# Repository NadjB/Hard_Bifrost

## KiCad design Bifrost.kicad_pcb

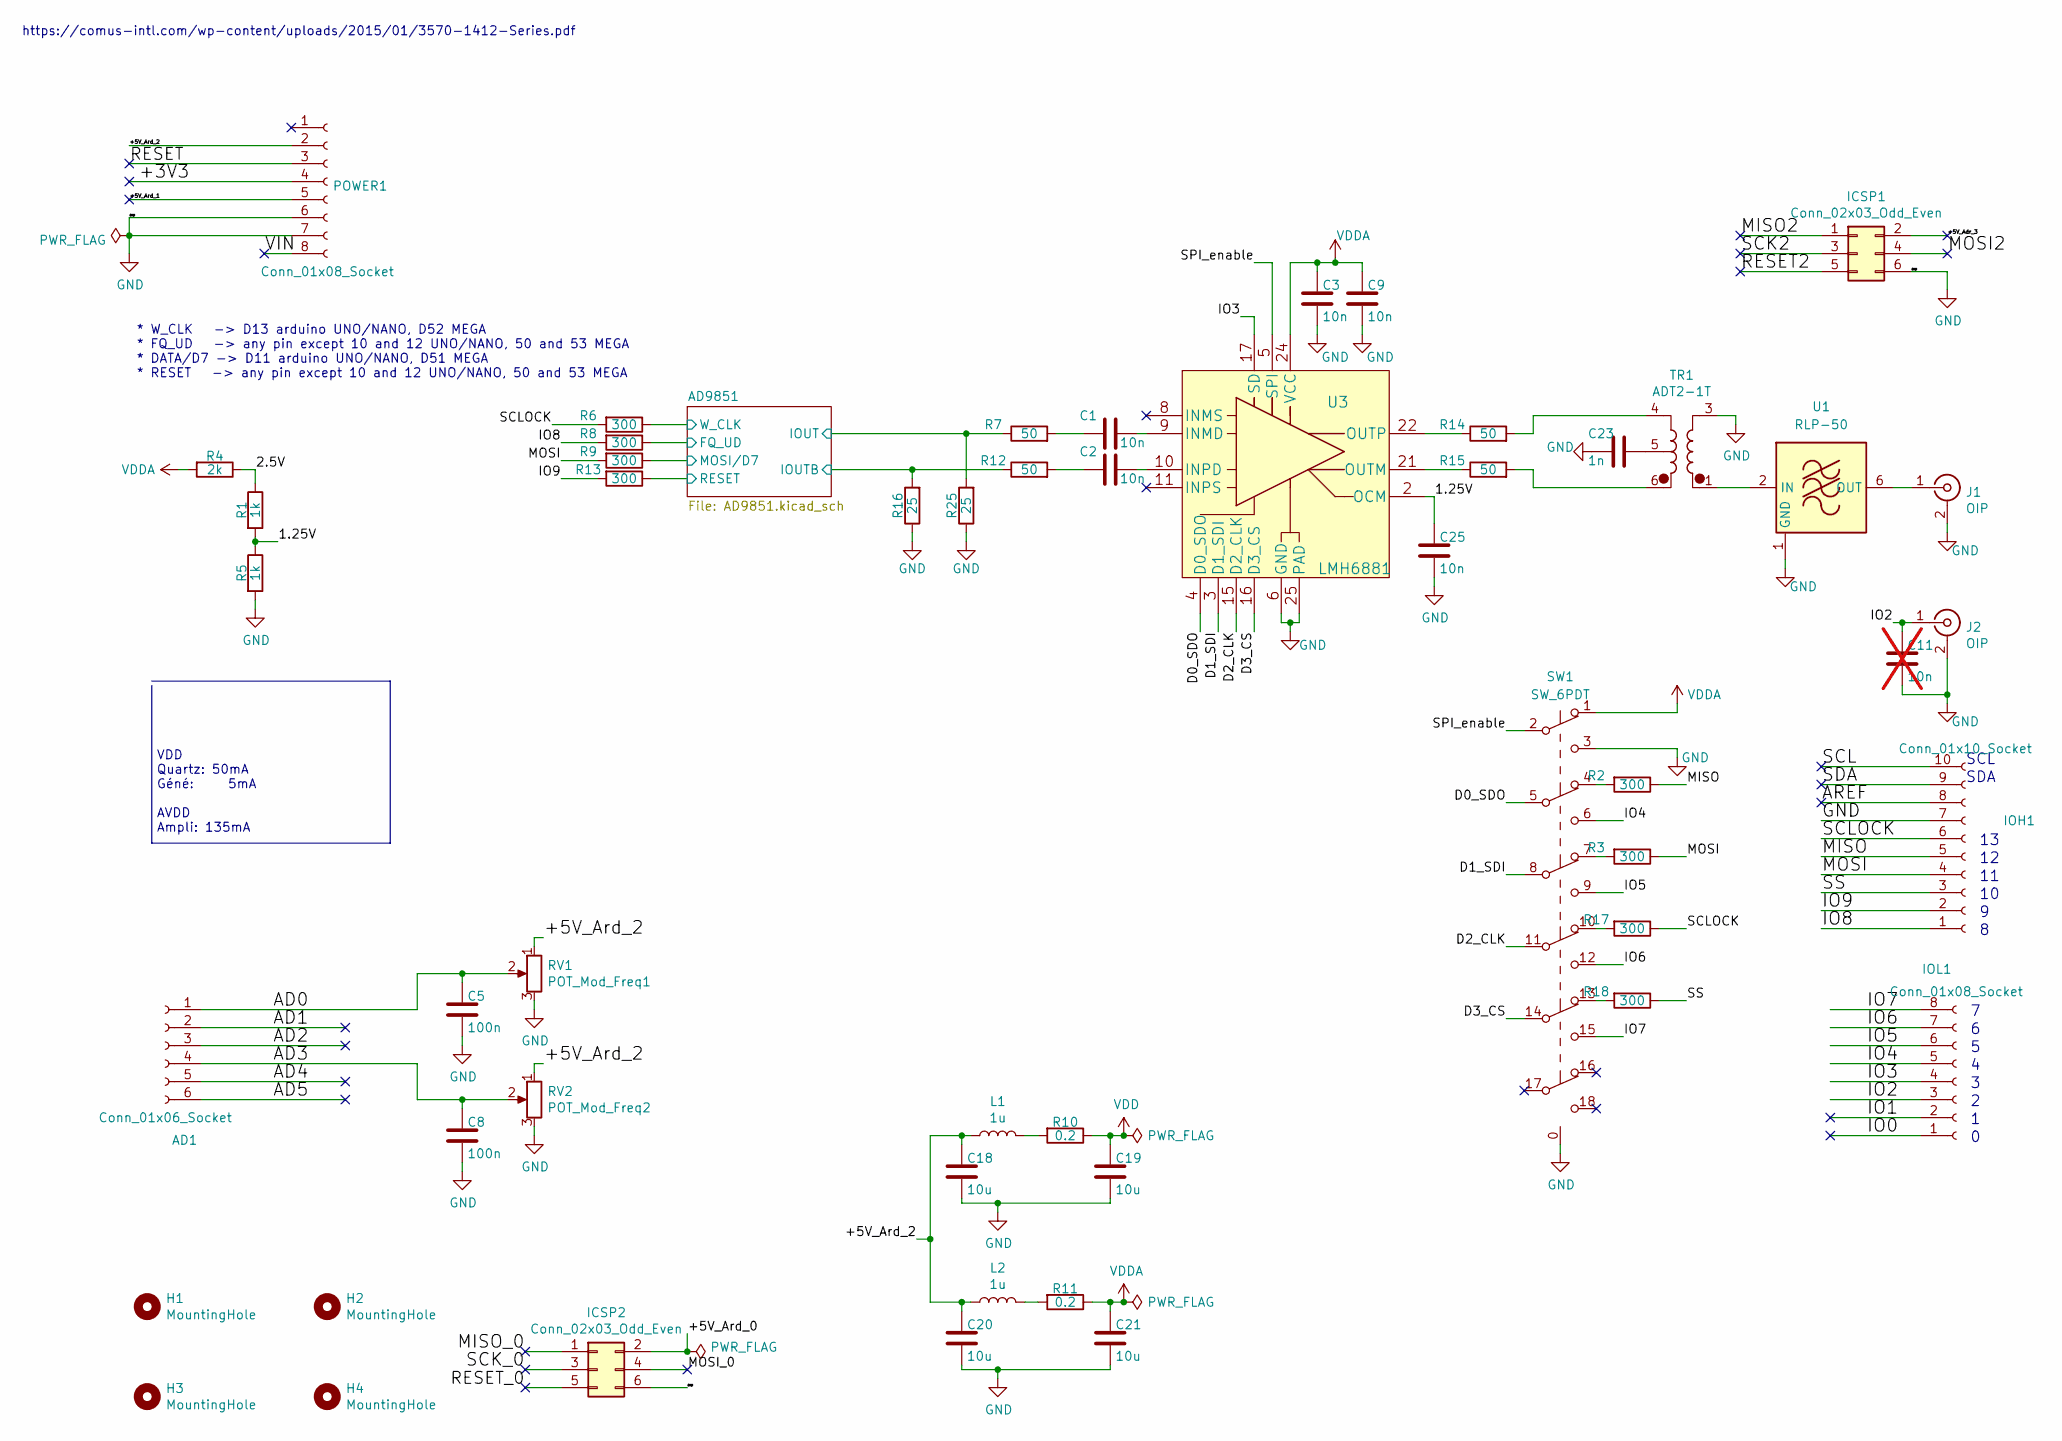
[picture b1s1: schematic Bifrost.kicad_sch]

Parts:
AD1: Conn_01x06_Socket; PinHeader_1x06_P2.54mm_Vertical
C1, C2, C3, C9, C25: 10n; C_0603_1608Metric_Pad1.08x0.95mm_HandSolder
C5, C8: 100n; C_0603_1608Metric_Pad1.08x0.95mm_HandSolder
C11: 10n; C_0603_1608Metric_Pad1.08x0.95mm_HandSolder; not fitted
C18, C19, C20, C21: 10u; C_1206_3216Metric_Pad1.33x1.80mm_HandSolder
C23: 1n; C_0603_1608Metric_Pad1.08x0.95mm_HandSolder
H1, H2, H3, H4: MountingHole; MountingHole_3mm
ICSP1, ICSP2: Conn_02x03_Odd_Even; PinSocket_2x03_P2.54mm_Vertical
IOH1: Conn_01x10_Socket; PinHeader_1x10_P2.54mm_Vertical
IOL1: Conn_01x08_Socket; PinHeader_1x08_P2.54mm_Vertical
J1, J2: OIP; SMA_Molex_73251-1153_EdgeMount_Horizontal
L1, L2: 1u; L_0603_1608Metric_Pad1.05x0.95mm_HandSolder
POWER1: Conn_01x08_Socket; PinHeader_1x08_P2.54mm_Vertical
R1, R5: 1k; R_0603_1608Metric_Pad0.98x0.95mm_HandSolder
R2, R3, R6, R8, R9, R13, R17, R18: 300; R_0603_1608Metric_Pad0.98x0.95mm_HandSolder
R4: 2k; R_0603_1608Metric_Pad0.98x0.95mm_HandSolder
R7, R12, R14, R15: 50; R_0603_1608Metric_Pad0.98x0.95mm_HandSolder
R10, R11: 0.2; R_0603_1608Metric_Pad0.98x0.95mm_HandSolder
R16, R25: 25; R_0603_1608Metric_Pad0.98x0.95mm_HandSolder
RV1: POT_Mod_Freq1; Potentiometer_Bourns_3266Y_Vertical
RV2: POT_Mod_Freq2; Potentiometer_Bourns_3266Y_Vertical
SW1: SW_6PDT; SW_EG6201
TR1: ADT2-1T; Mini-Circuits_CD542_H2.84mm
U1: RLP-50; Mini-Circuits_GP1212_LandPatternPL-176
U3: LMH6881; WQFN-24-1EP_4x4mm_P0.5mm_EP2.45x2.45mm_ThermalVias

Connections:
/1.25V: C25.2, R1.2, R5.1, U3.2 (OCM)
/2.5V: R1.1, R4.1
/+3V3: POWER1.4
/+5V_Adr_3: ICSP1.2
/+5V_Ard_0: ICSP2.2
/+5V_Ard_1: POWER1.5
/+5V_Ard_2: C18.2, C20.2, L1.1, L2.1, POWER1.2, RV1.1, RV2.1
/AD0: AD1.1, C5.2, RV1.2
/AD1: AD1.2
/AD2: AD1.3
/AD3: AD1.4, C8.2, RV2.2
/AD4: AD1.5
/AD5: AD1.6
/AD9851/FQ_UD: R8.1; also elsewhere on the board
/AD9851/IOUT: R7.1, R25.2; also elsewhere on the board
/AD9851/IOUTB: R12.1, R16.2; also elsewhere on the board
/AD9851/MOSI/D7: R9.1; also elsewhere on the board
/AD9851/RESET: R13.1; also elsewhere on the board
/AD9851/W_CLK: R6.1; also elsewhere on the board
/AREF: IOH1.8
/D0_SDO: SW1.5 (B), U3.4 (D0_SDO)
/D1_SDI: SW1.8 (B), U3.3 (D1_SDI)
/D2_CLK: SW1.11 (B), U3.15 (D2_CLK)
/D3_CS: SW1.14 (B), U3.16 (D3_CS)
/IO0: IOL1.1
/IO1: IOL1.2
/IO2: C11.2, IOL1.3, J2.1 (In)
/IO3: IOL1.4, U3.17 (SD)
/IO4: IOL1.5, SW1.6 (C)
/IO5: IOL1.6, SW1.9 (C)
/IO6: IOL1.7, SW1.12 (C)
/IO7: IOL1.8, SW1.15 (C)
/IO8: IOH1.1, R8.2
/IO9: IOH1.2, R13.2
/MISO: IOH1.5, R2.1
/MISO2: ICSP1.1
/MISO_0: ICSP2.1
/MOSI: IOH1.4, R3.1, R9.2
/MOSI2: ICSP1.4
/MOSI_0: ICSP2.4
/RESET: POWER1.3
/RESET2: ICSP1.5
/RESET_0: ICSP2.5
/SCK2: ICSP1.3
/SCK_0: ICSP2.3
/SCL: IOH1.10
/SCLOCK: IOH1.6, R6.2, R17.1
/SDA: IOH1.9
/SPI_enable: SW1.2 (B), U3.5 (SPI)
/SS: IOH1.3, R18.1
/VIN: POWER1.8
GND: C3.1, C5.1, C8.1, C9.1, C11.1, C18.1, C19.1, C20.1, C21.1, C23.1, C25.1, ICSP1.6, ICSP2.6, IOH1.7, J1.2 (Ext), J2.2 (Ext), POWER1.6, POWER1.7, R5.2, R16.1, R25.1, RV1.3, RV2.3, SW1.0, SW1.3 (C), TR1.3, U1.1 (GND), U1.3 (GND), U1.4 (GND), U1.5 (GND), U1.7 (GND), U1.8 (GND), U3.6 (GND), U3.7 (GND), U3.12 (GND), U3.13 (GND), U3.25 (PAD); also elsewhere on the board
unnamed: C1.1, R7.2
unnamed: C2.1, R12.2
unnamed: C23.2, TR1.5
unnamed: J1.1 (In), U1.6 (OUT)
unnamed: L1.2, R10.2
unnamed: L2.2, R11.2
unnamed: R2.2, SW1.4 (A)
unnamed: R3.2, SW1.7 (A)
unnamed: R14.2, TR1.4
unnamed: R15.2, TR1.6
unnamed: R17.2, SW1.10 (A)
unnamed: R18.2, SW1.13 (A)
unnamed: TR1.1, U1.2 (IN)
unnamed: C1.2, U3.9 (INMD)
unnamed: C2.2, U3.10 (INPD)
unnamed: R15.1, U3.21 (OUTM)
unnamed: R14.1, U3.22 (OUTP)
VDD: C19.2, R10.1; also elsewhere on the board
VDDA: C3.2, C9.2, C21.2, R4.2, R11.1, SW1.1 (A), U3.19 (VCC), U3.20 (VCC), U3.23 (VCC), U3.24 (VCC)

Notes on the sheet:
VDD Quartz: 50mA Géné: 5mA AVDD Ampli: 135mA
SDA
https://comus-intl.com/wp-content/uploads/2015/01/3570-1412-Series.pdf
* W_CLK -> D13 arduino UNO/NANO, D52 MEGA * FQ_UD -> any pin except 10 and 12 UNO/NANO, 50 and 53 MEGA * DATA/D7 -> D11 arduino UNO/NANO, D51 MEGA * RESET -> any pin except 10 and 12 UNO/NANO, 50 and 53 MEGA
SCL

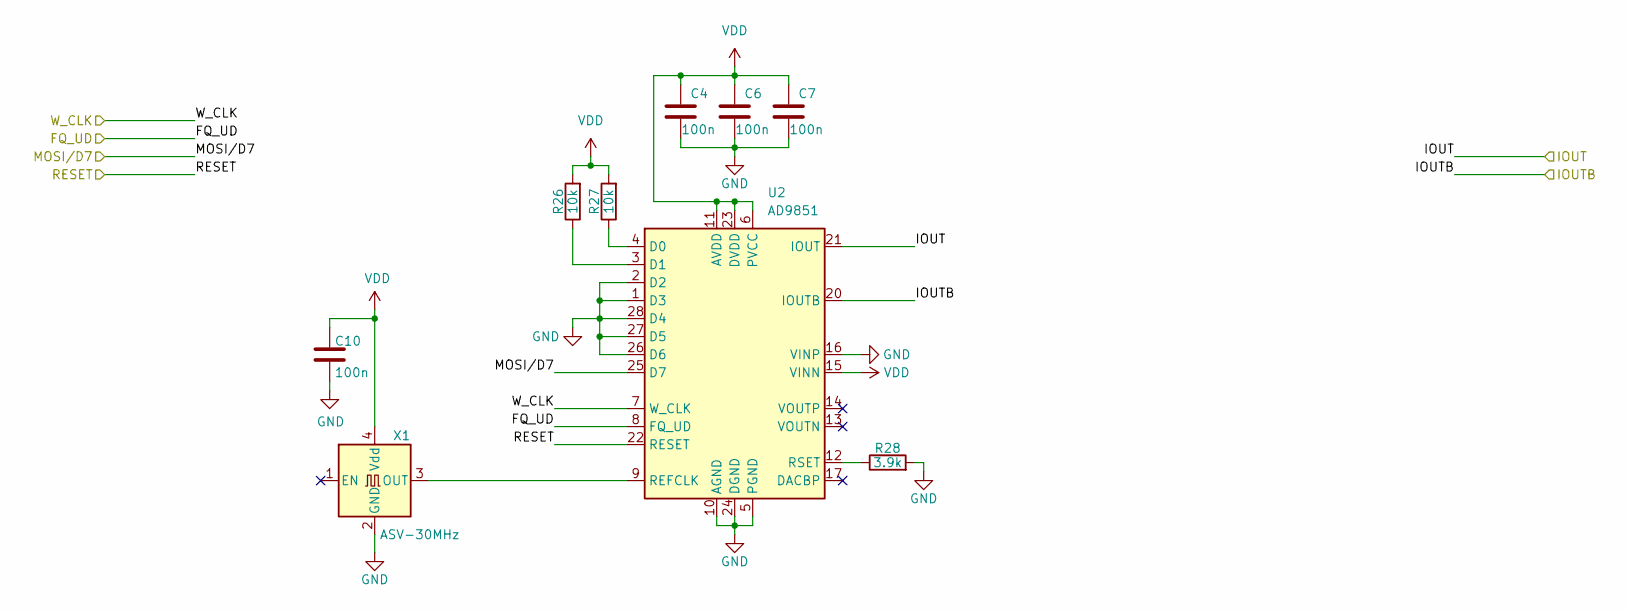
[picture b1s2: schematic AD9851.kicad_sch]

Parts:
C4, C6, C7, C10: 100n; C_0603_1608Metric_Pad1.08x0.95mm_HandSolder
R26, R27: 10k; R_0603_1608Metric_Pad0.98x0.95mm_HandSolder
R28: 3.9k; R_0603_1608Metric_Pad0.98x0.95mm_HandSolder
U2: AD9851; SSOP-28_5.3x10.2mm_P0.65mm
X1: ASV-30MHz; Oscillator_SMD_Abracon_ASV-4Pin_7.0x5.1mm

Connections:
/AD9851/FQ_UD: U2.8 (FQ_UD); also elsewhere on the board
/AD9851/IOUT: U2.21 (IOUT); also elsewhere on the board
/AD9851/IOUTB: U2.20 (IOUTB); also elsewhere on the board
/AD9851/MOSI/D7: U2.25 (D7); also elsewhere on the board
/AD9851/RESET: U2.22 (RESET); also elsewhere on the board
/AD9851/W_CLK: U2.7 (W_CLK); also elsewhere on the board
GND: C4.2, C6.2, C7.2, C10.1, R28.2, U2.1 (D3), U2.2 (D2), U2.5 (PGND), U2.10 (AGND), U2.16 (VINP), U2.19 (AGND), U2.24 (DGND), U2.26 (D6), U2.27 (D5), U2.28 (D4), X1.2 (GND); also elsewhere on the board
unnamed: R27.1, U2.4 (D0)
unnamed: R26.1, U2.3 (D1)
unnamed: U2.9 (REFCLK), X1.3 (OUT)
unnamed: R28.1, U2.12 (RSET)
VDD: C4.1, C6.1, C7.1, C10.2, R26.2, R27.2, U2.6 (PVCC), U2.11 (AVDD), U2.15 (VINN), U2.18 (AVDD), U2.23 (DVDD), X1.4 (Vdd); also elsewhere on the board

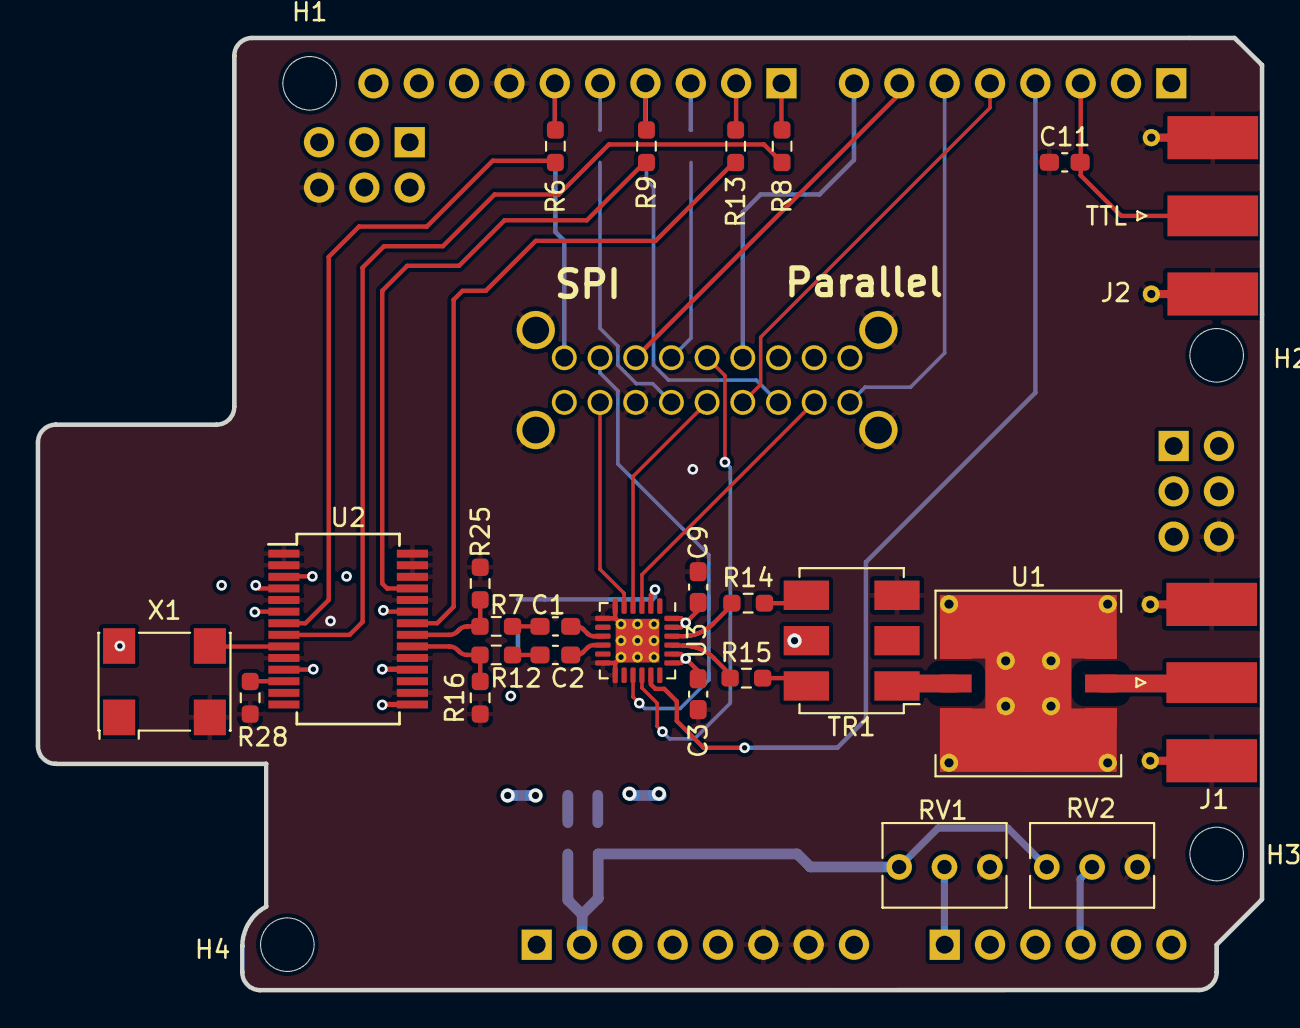
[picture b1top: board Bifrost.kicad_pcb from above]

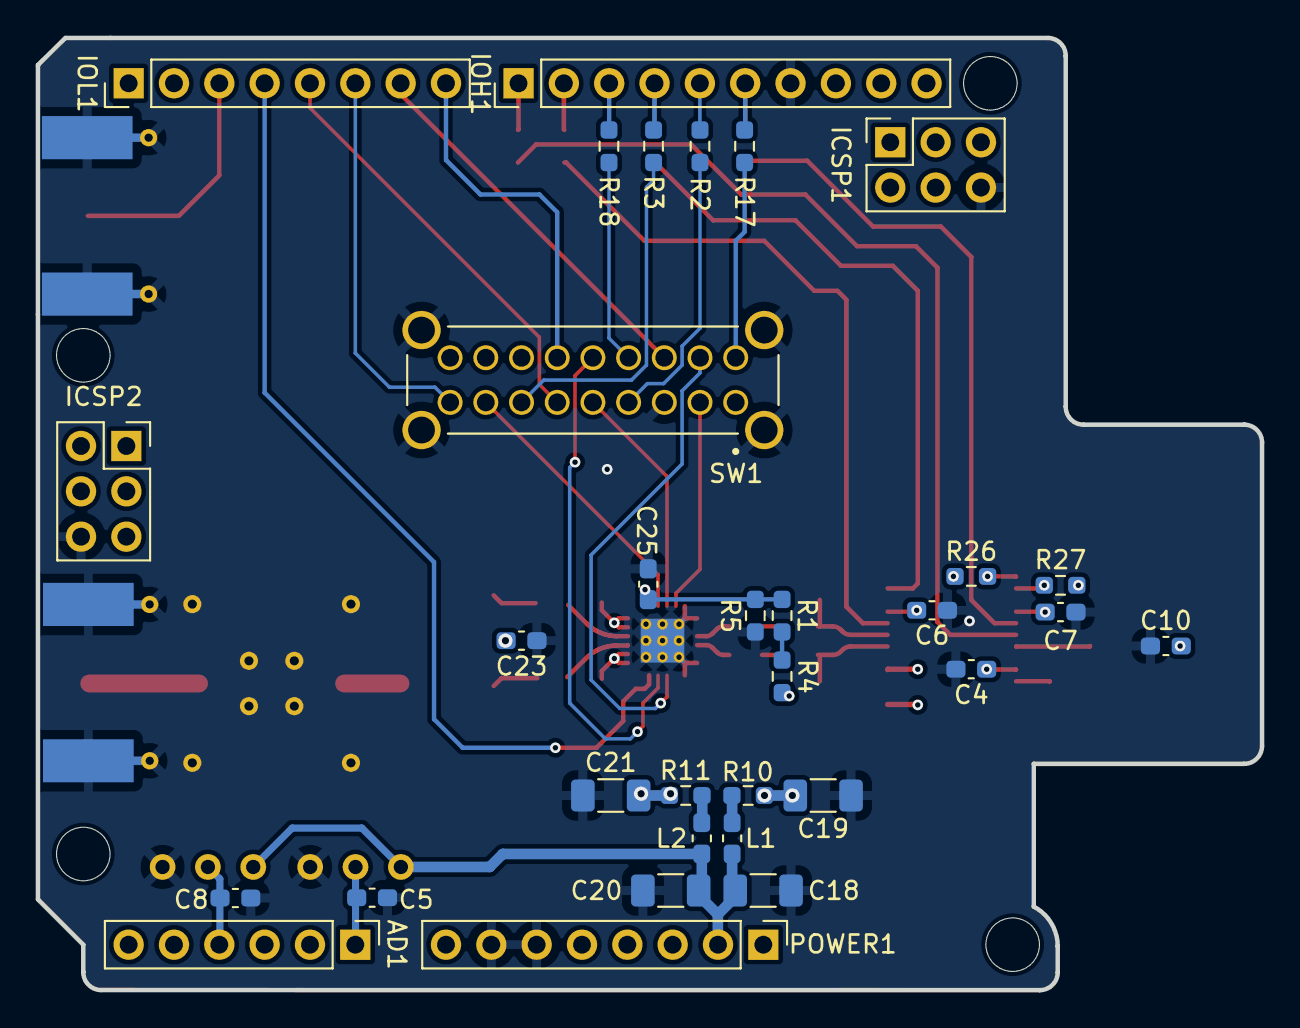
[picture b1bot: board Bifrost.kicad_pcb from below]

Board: 4 copper layers, 68.6 x 53.3 mm, 61 parts (32 on the bottom side), 52 nets.

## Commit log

2021-07-01 Made the HMC900 single ended in/out
2021-07-20 Corrected errors from single ended transition
2021-07-20 deleted superfluous components and began routing
2021-07-20 passage 0402 => 0603
2021-07-20 Changed power connector to barrel jack and Cal connector to pinhead
2021-07-20 Changed transfo reference from gnd to 2.5v because ds1085 goes from 0 to 5v
2021-07-20 Made it so there was only one output and change the SMA (to a sourceable one)
2021-07-21 Corrected SDA & SCL Pins progressed the routing
2021-07-21 Changed input transformer reference to 2.5v
2021-07-21 Added docs
2021-07-21 Straitened things before restarting routing
2021-07-22 v0 Routing done
2021-07-22 Rounded tracks
2021-07-22 Teardroped
2021-07-26 Via fencing
2021-07-29 Added BPF-E16+
2021-07-29 Added soldering options
2021-07-29 Added Logic gate buffer for the oscillator
2021-07-29 Added filtering capa and rearanged analogue in (A1=>A4)
2021-07-29 Added options for the tranfo
2021-07-30 reorganized to match power consumption
2021-07-30 added cavalier on the oscillator's power
2021-07-30 Connected the oscillators enable to the arduino
2021-08-03 added the option to switch HMC860 for HMC1060
2021-08-04 Added capacitors on potars
2021-08-05 Rearranged the serigraphs
2021-08-06 Bifrost_v1.0 launched to fab
2021-08-07 added the ...-cache.lib and HMC1060's doc
2021-08-27 As implemented for v1
2021-08-27 removed unused options added aop at the output
2021-08-30 output tranfo and aop work around vdd/2 caped aop's amplification at 9dB
2021-09-06 switched to "AD5932" from "ds1085 & hmc900" Removed external power supply
2021-09-10 Changed the pins ad5932<==>arduino to avoide Rx & Tx
2021-09-13 added a second ad5932
2021-09-13 Added the doc for the AD5932 and its oscillator
2021-09-15 Made a AVDD and DVDD Put an offset on the output off the signal generator
2021-09-16 Added fixed gain amplifiers Tweaked the filtering of AVDD & DVDD Began placing componants Put in feuille hierarchique
2021-09-16 addendum feuille hierarchique
2021-09-17 Progressed in placement
2021-09-21 Implemented the LMH6881 instead of the AD8000 Continued routing
2021-09-28 Deleted the fix gain amlifier
2021-09-28 put the AD5932's Standby to the ground
2021-10-06 Changed gain pins for the LMH6881 and changed alim for the oscillator
2021-10-07 Changed inductor and reststor on power filtration to limit DDP
2021-10-07 v1.0 of the routing
2021-10-13 Position des jumper/switch
2021-11-02 Optimized routing
2021-11-03 Added thermal vias for the LMH6881 and re-routed to accommodate
2021-11-03 Same as the last part 2
2021-11-05 Cleaning
2021-11-08 Bifrost_v2.0 launched to fab Modified LMH6881's thermal vias Rotated GND pads to better propagate GND
2021-11-16 Added notes to switch the position off the switches and renamed doc
2021-11-16 Added doc for the AD9851
2021-11-30 Added SCLF-21.4+ Deleted the superfluous AD5932 Changed the switches for the LMH881 gain from D0&D1 to D2&D3 Re-routed
2021-12-01 Began implementing AD9851
2021-12-09 Made the 2 DS1085 signals merge before the filter Looped the filter's 1st output to the now liberated 2nd input to double the filtration Added a protection diode before the filter
2022-03-03 Switched to KiCad 6 Replaced AD5932 by AD9851 Moved amplifier switches to D0&D3
2022-03-07 Switch to Kicad 6
2022-03-07 same
2022-03-07 Added filters on output wired the option to have all of the amplifier parallel bits connected
2022-03-08 Done routing and serigraphie
2022-03-09 Finished serigraphie IBOM generated and components sourced
2022-03-09 removed .kicad_prl
2022-03-21 Envoyé en fabrication Bifrost_v3.0
2022-04-27 As implemented
2022-05-04 Connected ampli's ShutDown pin
2023-06-02 Switched to Kicad 7
2023-06-02 Replaced SPI selection resistors with a 6PDT (LMH6881 pins 3, 4, 5, 15, 16)
2023-06-12 Implemented change on pcb Updated Schematics symbols to Kicad 7 standards (Female=>Socket...)
2023-06-12 Added TTL output
2023-07-12 As impemented v2
